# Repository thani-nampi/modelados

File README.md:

# modelados

Repositorios de los modelados del chaleco, case y placas.

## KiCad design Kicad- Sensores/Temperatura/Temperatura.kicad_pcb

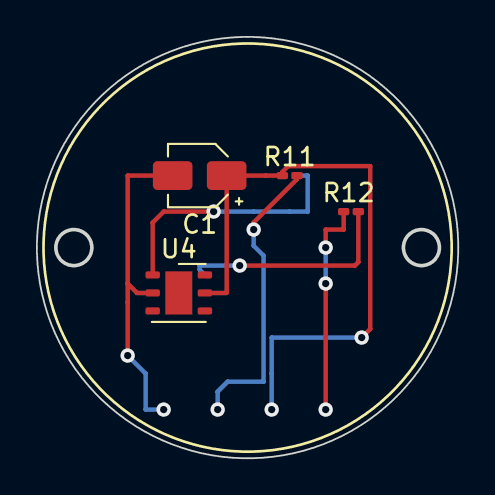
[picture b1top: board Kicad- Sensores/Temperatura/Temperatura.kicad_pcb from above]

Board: 2 copper layers, 23.3 x 23.3 mm, 4 parts (0 on the bottom side), 4 nets.

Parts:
C1: 0.1μF; CP_Elec_3x5.4
R11, R12: 10kμ; R_0201_0603Metric_Pad0.64x0.40mm_HandSolder
U4: Si7021-A20; DFN-6-1EP_3x3mm_P1mm_EP1.5x2.4mm

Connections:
GND: C1.2, U4.2
unnamed: C1.1, R11.1, U4.VDD
unnamed: R11.2, U4.SDA
unnamed: R12.2, U4.SCL

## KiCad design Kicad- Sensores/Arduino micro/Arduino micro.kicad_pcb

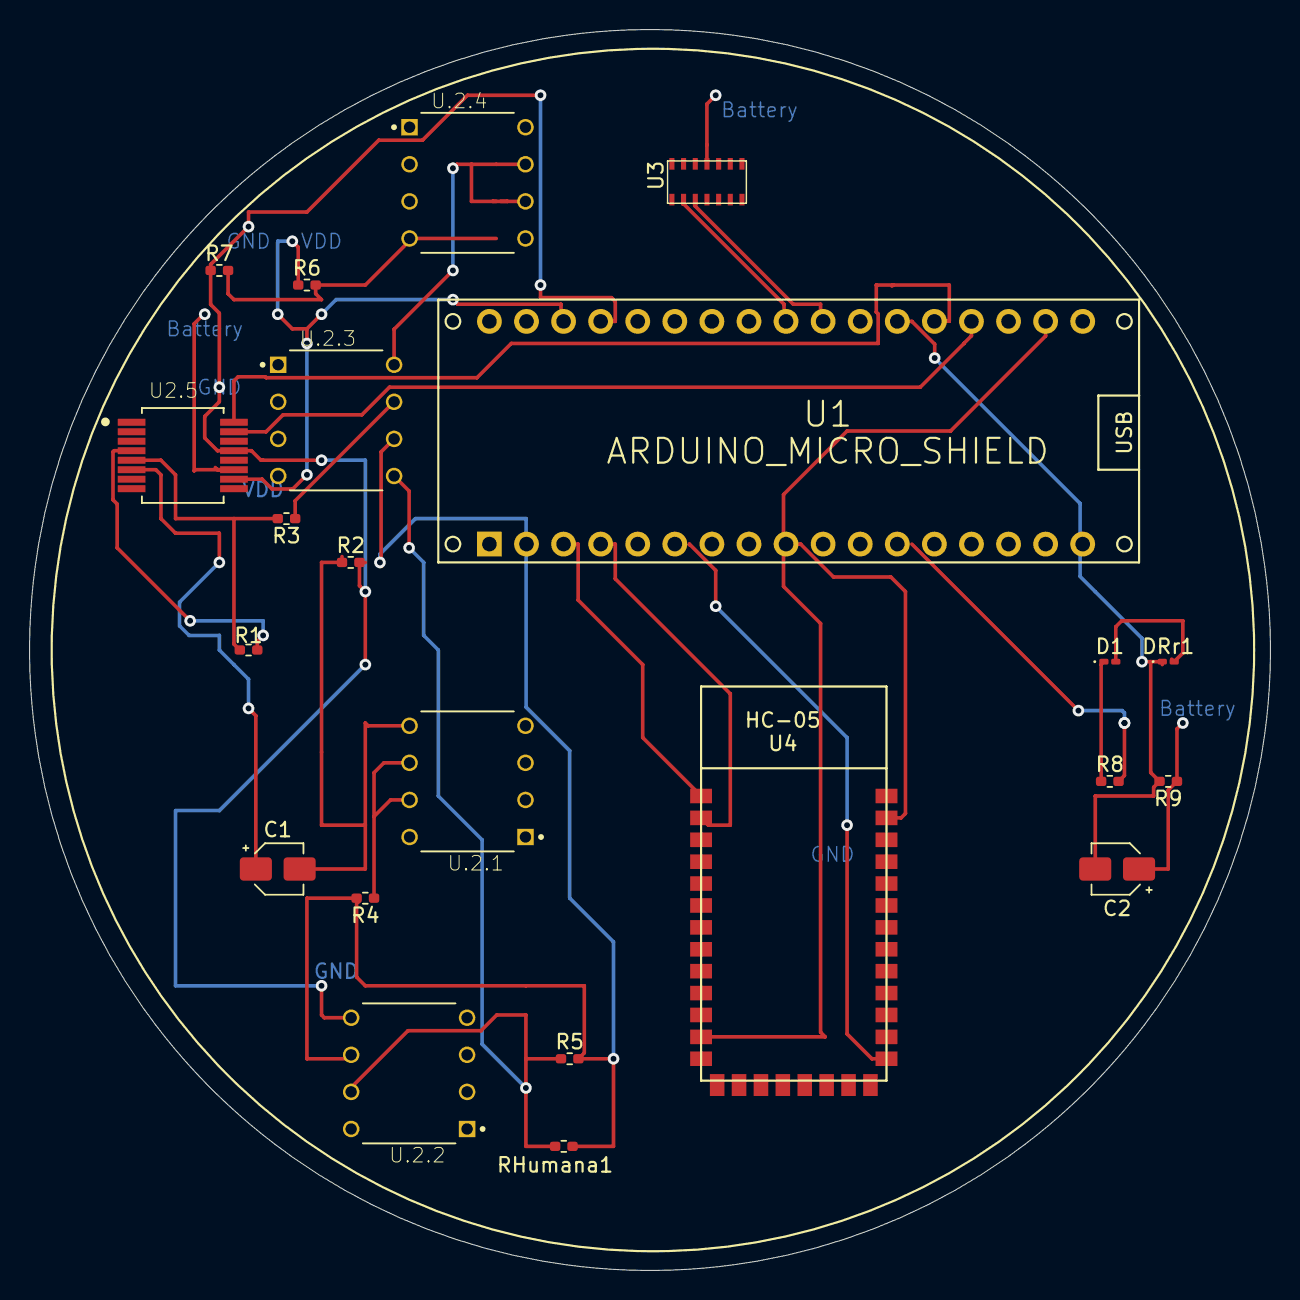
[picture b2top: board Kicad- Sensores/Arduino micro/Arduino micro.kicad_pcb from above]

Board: 2 copper layers, 85.0 x 85.0 mm, 22 parts (0 on the bottom side), 26 nets.

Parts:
C1: 1 uF; CP_Elec_3x5.4
C2: 100 nF; CP_Elec_3x5.4
D1: --; LED_0201_0603Metric_Pad0.64x0.40mm_HandSolder
DRr1: -; LED_0201_0603Metric_Pad0.64x0.40mm_HandSolder
HC-05: U4; HC-05
R1: 100 k100 Ω; R_0402_1005Metric_Pad0.72x0.64mm_HandSolder
R2, R9: 100 kΩ; R_0402_1005Metric_Pad0.72x0.64mm_HandSolder
R3: 620 k Ω; R_0402_1005Metric_Pad0.72x0.64mm_HandSolder
R4, R5: 10 k; R_0402_1005Metric_Pad0.72x0.64mm_HandSolder
R6: 1MΩ; R_0402_1005Metric_Pad0.72x0.64mm_HandSolder
R7: 10k; R_0402_1005Metric_Pad0.72x0.64mm_HandSolder
R8: 100 Ω; R_0402_1005Metric_Pad0.72x0.64mm_HandSolder
RHumana1: RHumana1; R_0402_1005Metric_Pad0.72x0.64mm_HandSolder
U1: ARDUINO_MICRO_SHIELD
U2.5: AD5933YRSZ-REEL7; SOP65P780X200-16N
U3: MAX30100
U.2.1, U.2.2, U.2.3, U.2.4: LF353N; DIP794W45P254L959H508Q8

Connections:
GND: R2.2, R7.1, U1.GND, U2.5.13, U.2.2.5
unnamed: C1.1, U2.5.6
unnamed: C1.2, R2.1, U.2.1.5
unnamed: C2.1, R9.1
unnamed: C2.2, DRr1.1, R9.2, U1.A2
unnamed: D1.1, R8.1
unnamed: D1.2, DRr1.2
unnamed: HC-05.1, U1.TX
unnamed: HC-05.2, U1.RX
unnamed: HC-05.12, U1.3.3V
unnamed: HC-05.22, U1.GND
unnamed: HC-05.33, U1.4
unnamed: R1.1, U2.5.4
unnamed: R1.2, R3.2, U2.5.5
unnamed: R3.1, U.2.3.7
unnamed: R4.1, U.2.1.6, U.2.1.7
unnamed: R4.2, R5.2, RHumana1.1, U.2.2.6, U.2.3.6
unnamed: R5.1, RHumana1.2, U.2.2.7, U.2.3.5
unnamed: R6.1, U1.VI, U2.5.10
unnamed: R6.2, R7.2, U.2.4.5
unnamed: R8.2, U1.7
unnamed: U1.A0, U2.5.15
unnamed: U1.A1, U2.5.16
unnamed: U1.A4, U3.3
unnamed: U1.A5, U3.2
unnamed: U.2.3.8, U.2.4.6, U.2.4.7

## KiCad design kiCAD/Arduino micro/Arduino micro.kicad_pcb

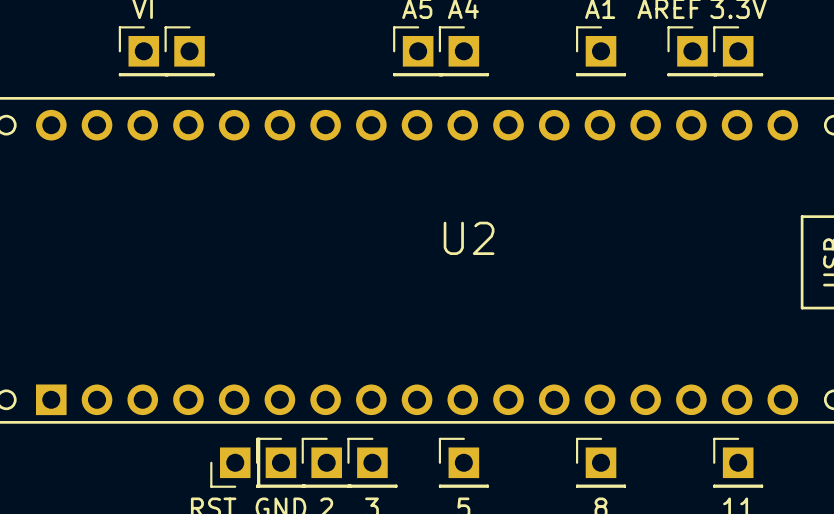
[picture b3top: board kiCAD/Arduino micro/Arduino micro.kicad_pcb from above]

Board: 2 copper layers, 15 parts (0 on the bottom side), 14 nets, no tracks yet.

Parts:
2, 3, 3.3V, 5, 8, 11: Conn_01x01_Male; PinHeader_1x01_P2.54mm_Vertical
A1, A4, A5: Conn_01x01_Male; PinHeader_1x01_P2.54mm_Vertical
AREF: Conn_01x01_Male; PinHeader_1x01_P2.54mm_Vertical
GND: Conn_01x01_Male; PinHeader_1x01_P2.54mm_Vertical
GND#2: Conn_01x01_Male; PinHeader_1x01_P2.54mm_Vertical
RST: Conn_01x01_Male; PinHeader_1x01_P2.54mm_Vertical
U2: ARDUINO_MICRO_SHIELD
VI: Conn_01x01_Male; PinHeader_1x01_P2.54mm_Vertical

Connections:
GND: U2.12, U2.13
unnamed: 2.1, U2.2
unnamed: 3.1, U2.3
unnamed: 3.3V.1, U2.3.3V
unnamed: 5.1, U2.5
unnamed: 8.1, U2.8
unnamed: 11.1, U2.11
unnamed: A1.1, U2.A1
unnamed: A4.1, U2.A4
unnamed: A5.1, U2.A5
unnamed: AREF.1, U2.AREF
unnamed: GND.1, GND#2.1, U2.GND
unnamed: RST.1, U2.RST
unnamed: U2.VI, VI.1

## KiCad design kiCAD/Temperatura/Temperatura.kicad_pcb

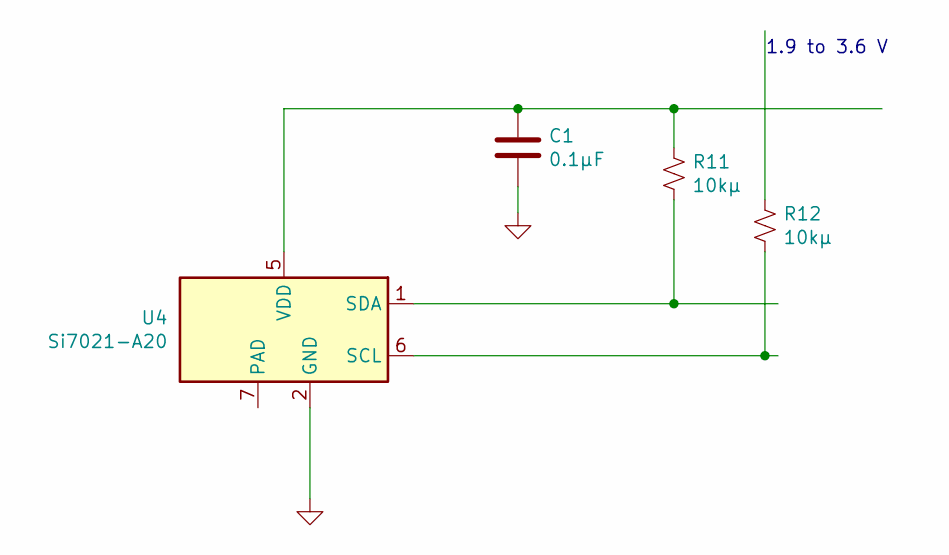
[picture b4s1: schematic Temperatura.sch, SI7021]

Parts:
C1: 0.1μF; CP_Elec_3x5.4
R11, R12: 10kμ; R_0201_0603Metric_Pad0.64x0.40mm_HandSolder
U4: Si7021-A20; DFN-6-1EP_3x3mm_P1mm_EP1.5x2.4mm

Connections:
GND: C1.2, U4.2 (GND)
unnamed: C1.1, R11.1, U4.5 (VDD)
unnamed: R11.2, U4.1 (SDA)
unnamed: R12.2, U4.6 (SCL)

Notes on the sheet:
1.9 to 3.6 V

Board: 2 copper layers, 4 parts (0 on the bottom side), 4 nets, no tracks yet.

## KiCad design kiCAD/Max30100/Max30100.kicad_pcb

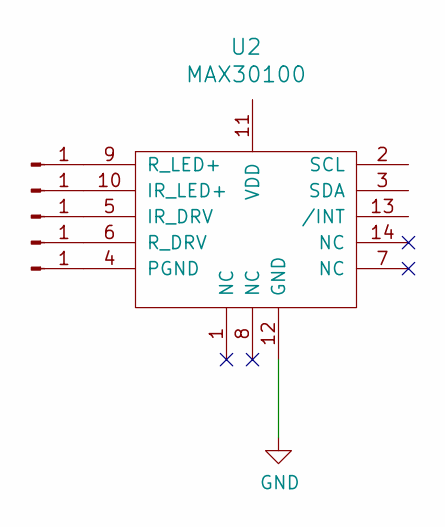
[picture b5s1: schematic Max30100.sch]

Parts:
J1, J2, J3, J4, J5: Conn_01x01_Male; PinHeader_1x01_P1.00mm_Vertical
U2: MAX30100

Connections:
GND: U2.12 (GND)
unnamed: J1.1, U2.9 (R_LED+)
unnamed: J2.1, U2.10 (IR_LED+)
unnamed: J3.1, U2.5 (IR_DRV)
unnamed: J4.1, U2.6 (R_DRV)
unnamed: J5.1, U2.4 (PGND)

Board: 2 copper layers, 6 parts (0 on the bottom side), 5 nets, no tracks yet.

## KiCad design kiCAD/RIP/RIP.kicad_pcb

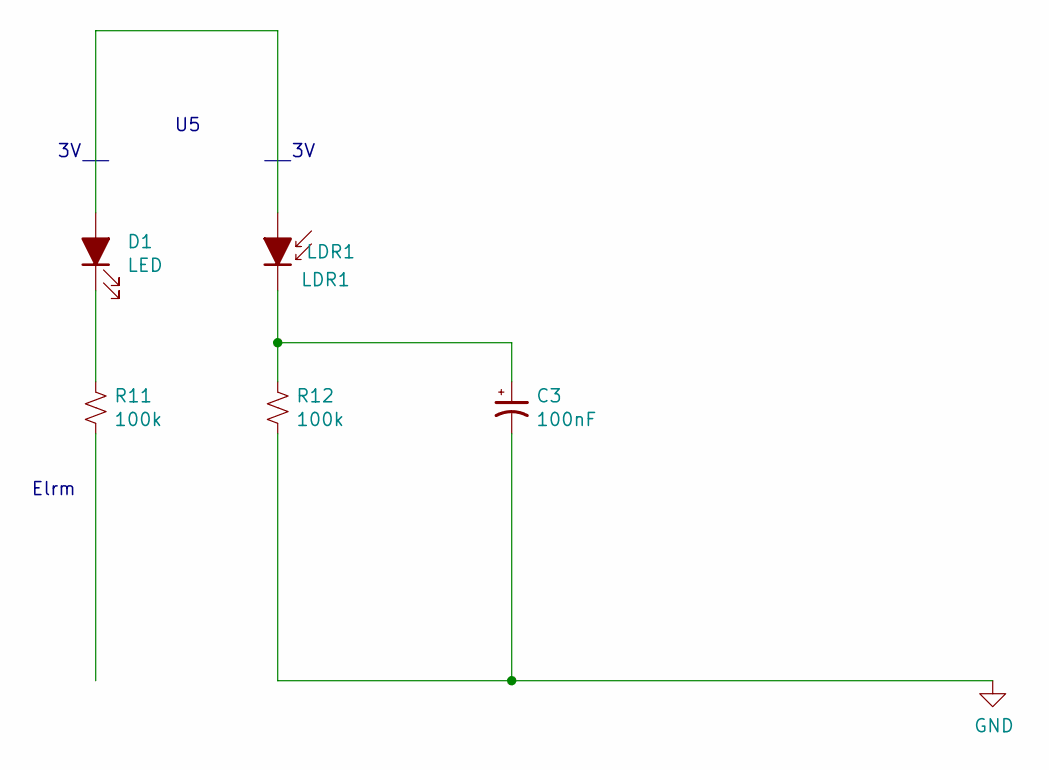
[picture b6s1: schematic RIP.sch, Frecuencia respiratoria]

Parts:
C3: 100nF; CP_Elec_3x5.4
D1: LED; LED_0201_0603Metric_Pad0.64x0.40mm_HandSolder
LDR1: LDR1; LED_0201_0603Metric_Pad0.64x0.40mm_HandSolder
R11, R12: 100k; R_0201_0603Metric_Pad0.64x0.40mm_HandSolder

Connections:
GND: C3.2, R12.2
unnamed: C3.1, LDR1.1 (K), R12.1
unnamed: D1.1 (K), R11.1
unnamed: D1.2 (A), LDR1.2 (A)

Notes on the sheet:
Elrm

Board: 2 copper layers, 5 parts (0 on the bottom side), 4 nets, no tracks yet.

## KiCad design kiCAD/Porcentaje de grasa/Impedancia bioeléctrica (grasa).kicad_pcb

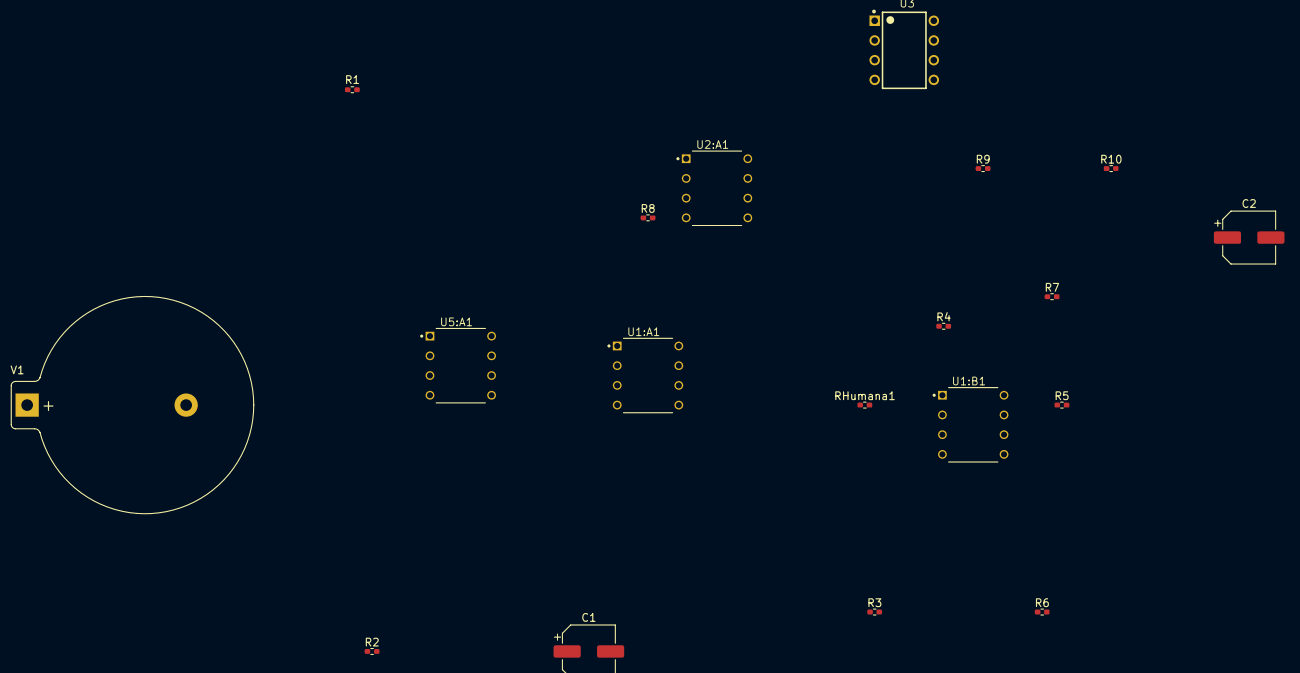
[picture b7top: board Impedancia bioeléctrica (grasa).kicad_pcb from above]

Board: 2 copper layers, 19 parts (0 on the bottom side), 11 nets, no tracks yet.

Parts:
C1: 1uF; CP_Elec_6.3x5.4
C2: 4.7uF; CP_Elec_6.3x5.4
R1: 100kΩ; R_0402_1005Metric_Pad0.72x0.64mm_HandSolder
R2: 100k; R_0402_1005Metric_Pad0.72x0.64mm_HandSolder
R3: 620kΩ; R_0402_1005Metric_Pad0.72x0.64mm_HandSolder
R4, R5, R6, R7: 1M; R_0402_1005Metric_Pad0.72x0.64mm_HandSolder
R8: 33K; R_0402_1005Metric_Pad0.72x0.64mm_HandSolder
R9: 33k; R_0402_1005Metric_Pad0.72x0.64mm_HandSolder
R10: 10k; R_0402_1005Metric_Pad0.72x0.64mm_HandSolder
RHumana1: 2500; R_0402_1005Metric_Pad0.72x0.64mm_HandSolder
U1:A1, U1:B1, U2:A1, U5:A1: LF353; DIP794W45P254L959H508Q8
U3: IL300; DIP762W50P254L977H451Q8
V1: 9V; BatteryHolder_Keystone_105_1x2430

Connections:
Earth: C1.1, R8.2, U3.2
GNDREF: C2.2, R3.2, R6.2
unnamed: C1.2, R2.2, V1.2
unnamed: C2.1, R10.1
unnamed: R1.1, V1.1
unnamed: R1.2, R2.1
unnamed: R3.1, R5.2, RHumana1.2
unnamed: R4.1, R7.2, RHumana1.1
unnamed: R5.1, R6.1
unnamed: R8.1, U3.4
unnamed: R9.1, R10.2, U3.5

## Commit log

2020-11-25 Carpeta kiCAD
2020-11-25 archivos inventor
2020-11-25 Modelados del Abrazo de Salud
2020-11-29 boton encendido
2020-12-02 Modelado del case de temperatura + planos
2020-12-09 kicad deleted
